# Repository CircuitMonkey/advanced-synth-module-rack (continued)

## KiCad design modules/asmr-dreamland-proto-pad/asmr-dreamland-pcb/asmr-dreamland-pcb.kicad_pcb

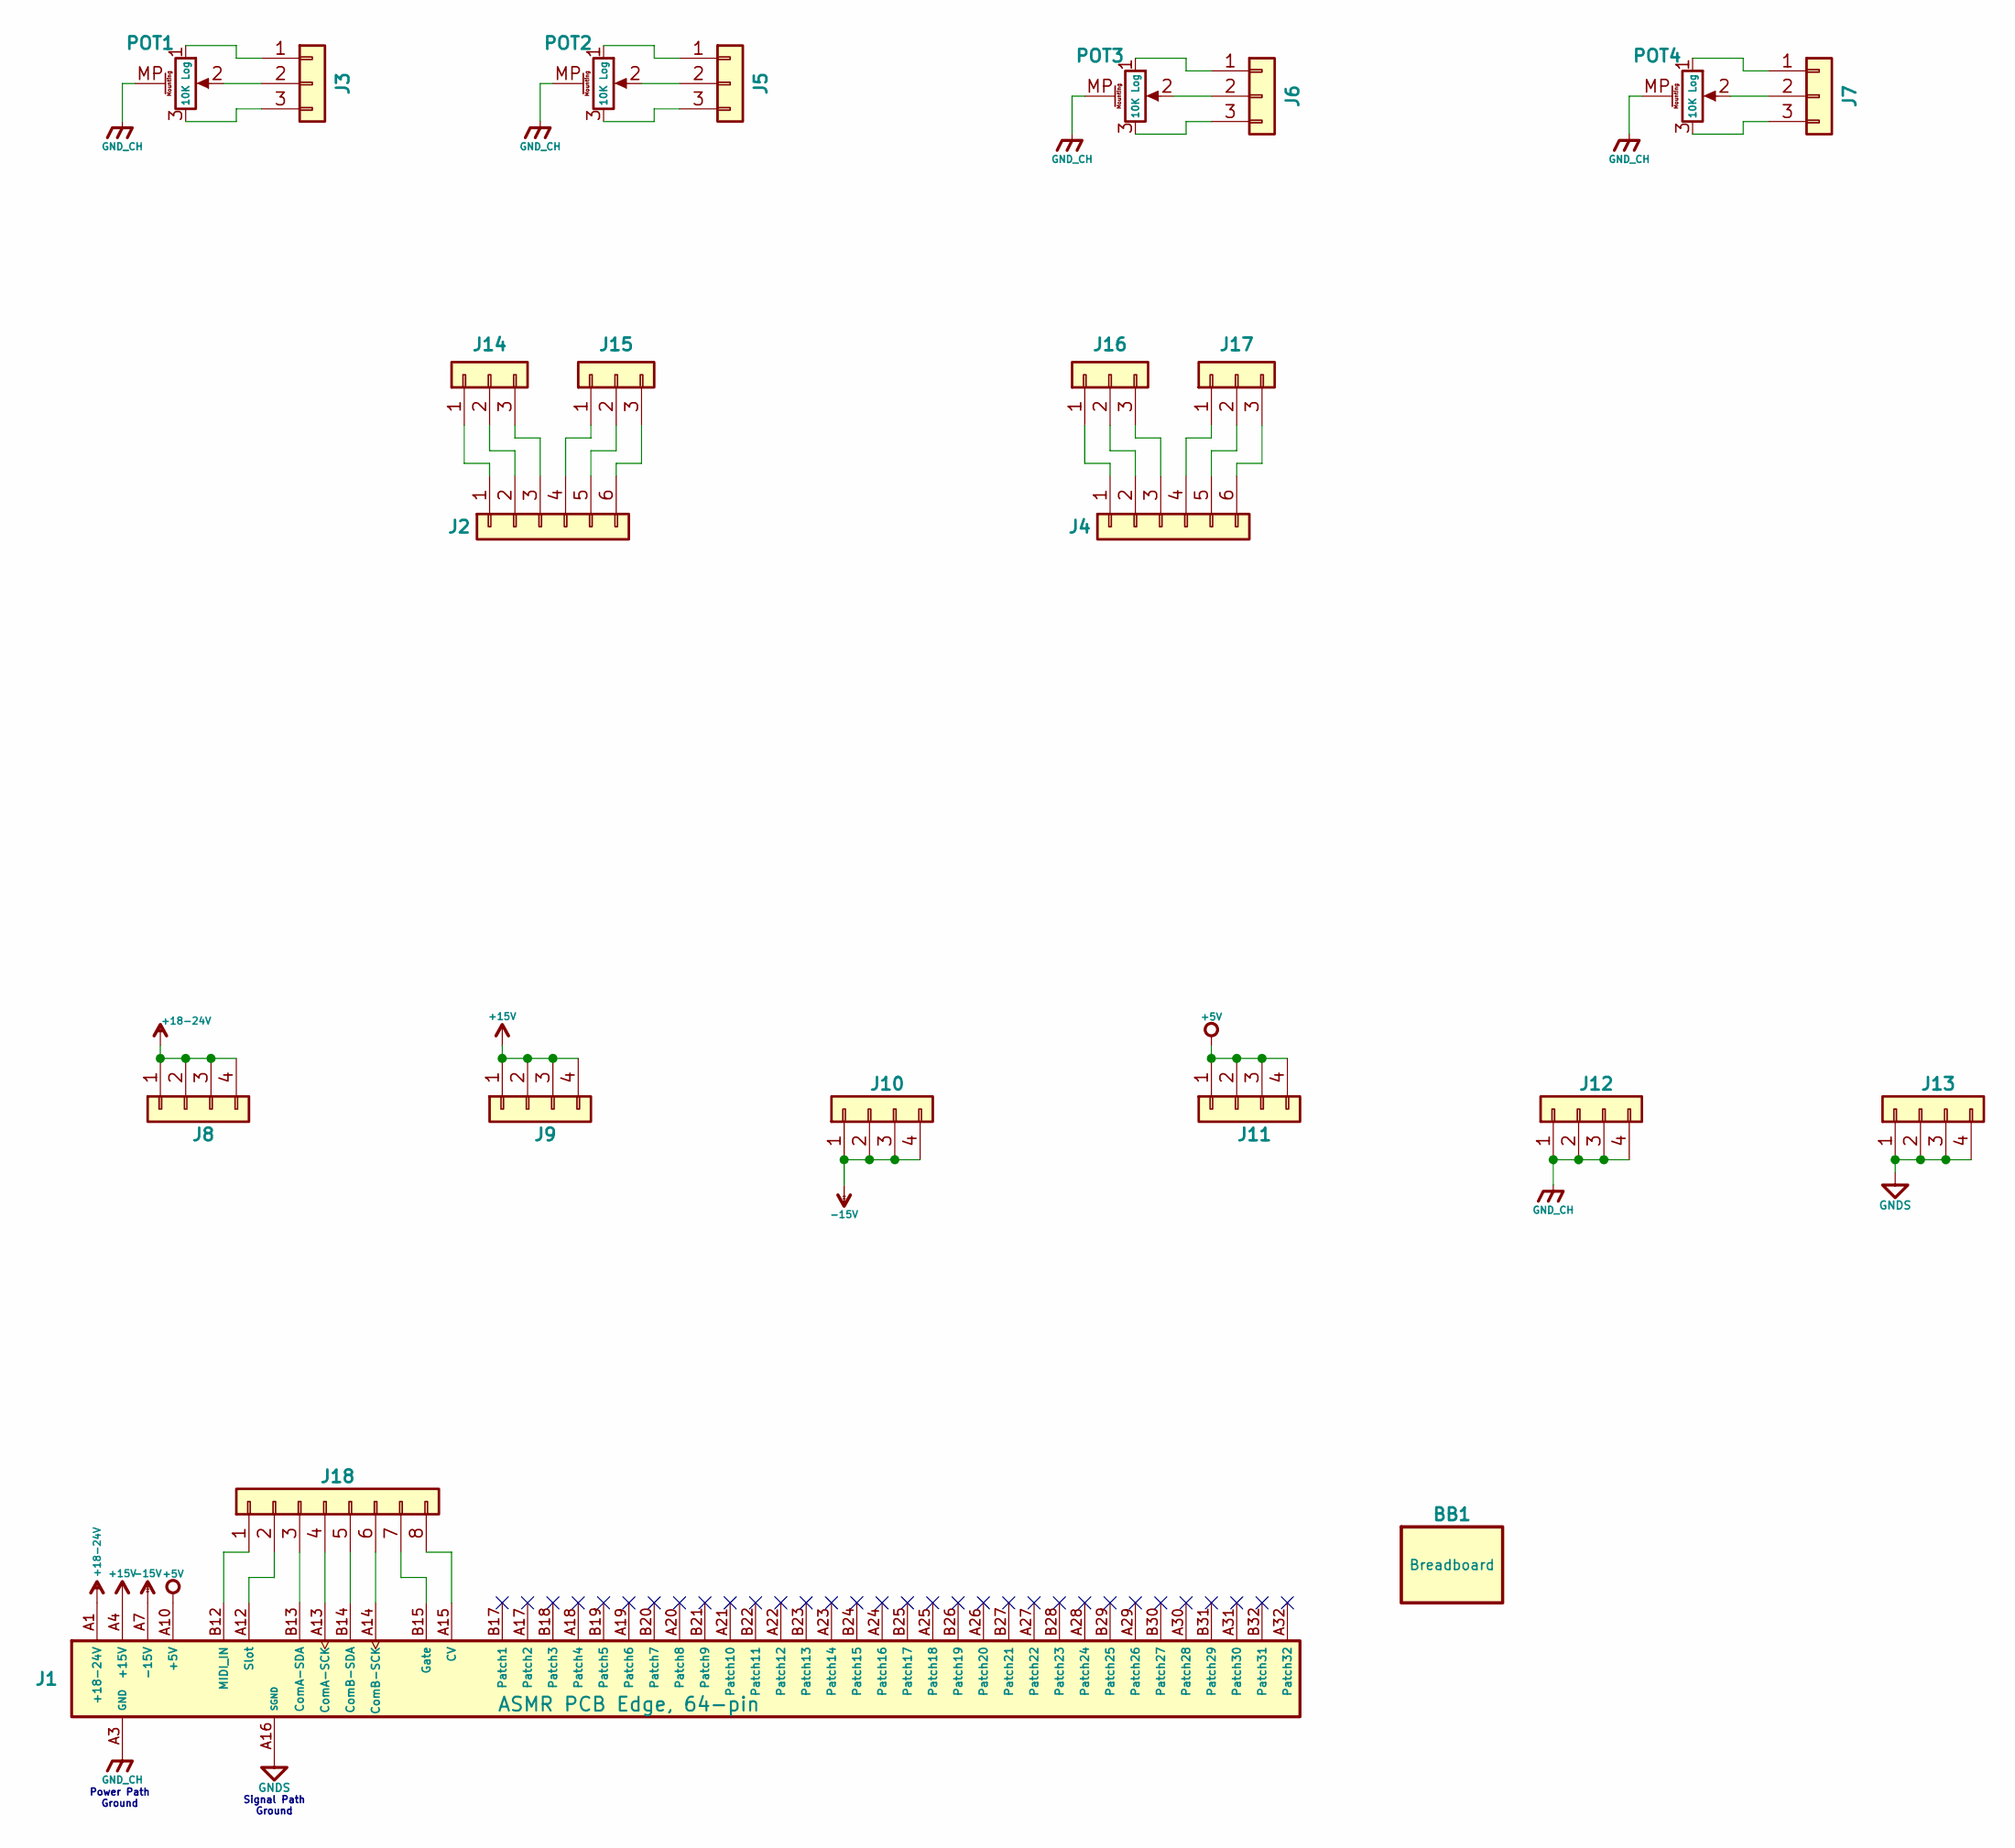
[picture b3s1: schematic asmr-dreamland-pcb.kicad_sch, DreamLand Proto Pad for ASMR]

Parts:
BB1: Breadboard; breadboard-84x55; MPN Tayda A-1427 (or similar)
J1: ASMR-Edge-64
J2, J4: Conn_01x06; PinSocket_1x06_P2.54mm_Vertical
J3, J5, J6, J7: Conn_01x03; PinSocket_1x03_P2.54mm_Vertical
J8, J9, J10, J11, J12, J13: Conn_01x10; PinSocket_1x04_P2.54mm_Vertical
J14, J15, J16, J17: Conn_01x03; PinHeader_1x03_P2.54mm_Vertical
J18: Conn_01x08; PinSocket_1x08_P2.54mm_Vertical
POT1, POT2, POT3, POT4: 10K Log; pot-thd-ra-11mm

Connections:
+5V: J1.A10 (+5V), J1.A11 (+5V), J1.B10 (+5V), J1.B11 (+5V), J11.1, J11.2, J11.3, J11.4
+15V: J1.A4 (+15V), J1.A5 (+15V), J1.B4 (+15V), J1.B5 (+15V), J9.1, J9.2, J9.3, J9.4
+18-24V: J1.A1 (+18-24V), J1.A2 (+18-24V), J1.B1 (+18-24V), J1.B2 (+18-24V), J8.1, J8.2, J8.3, J8.4
-15V: J1.A7 (-15V), J1.A8 (-15V), J1.B7 (-15V), J1.B8 (-15V), J10.1, J10.2, J10.3, J10.4
GNDS: J1.A16 (SGND), J1.B16 (SGND), J13.1, J13.2, J13.3, J13.4
GND_CH: J1.A3 (GND), J1.A6 (GND), J1.A9 (GND), J1.B3 (GND), J1.B6 (GND), J1.B9 (GND), J12.1, J12.2, J12.3, J12.4, POT1.MP (MountPin), POT2.MP (MountPin), POT3.MP (MountPin), POT4.MP (MountPin)
unnamed: J1.A15 (CV), J18.8
unnamed: J1.A13 (ComA-SCK), J18.4
unnamed: J1.B13 (ComA-SDA), J18.3
unnamed: J1.A14 (ComB-SCK), J18.6
unnamed: J1.B14 (ComB-SDA), J18.5
unnamed: J1.B15 (Gate), J18.7
unnamed: J1.B12 (MIDI_IN), J18.1
unnamed: J1.A12 (Slot), J18.2
unnamed: J3.1, POT1.1
unnamed: J3.2, POT1.2
unnamed: J3.3, POT1.3
unnamed: J5.1, POT2.1
unnamed: J5.2, POT2.2
unnamed: J5.3, POT2.3
unnamed: J6.1, POT3.1
unnamed: J6.2, POT3.2
unnamed: J6.3, POT3.3
unnamed: J7.1, POT4.1
unnamed: J7.2, POT4.2
unnamed: J7.3, POT4.3
unnamed: J2.1, J14.1
unnamed: J2.2, J14.2
unnamed: J2.3, J14.3
unnamed: J2.4, J15.1
unnamed: J2.5, J15.2
unnamed: J2.6, J15.3
unnamed: J4.1, J16.1
unnamed: J4.2, J16.2
unnamed: J4.3, J16.3
unnamed: J4.4, J17.1
unnamed: J4.5, J17.2
unnamed: J4.6, J17.3

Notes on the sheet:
Power Path Ground
Signal Path Ground

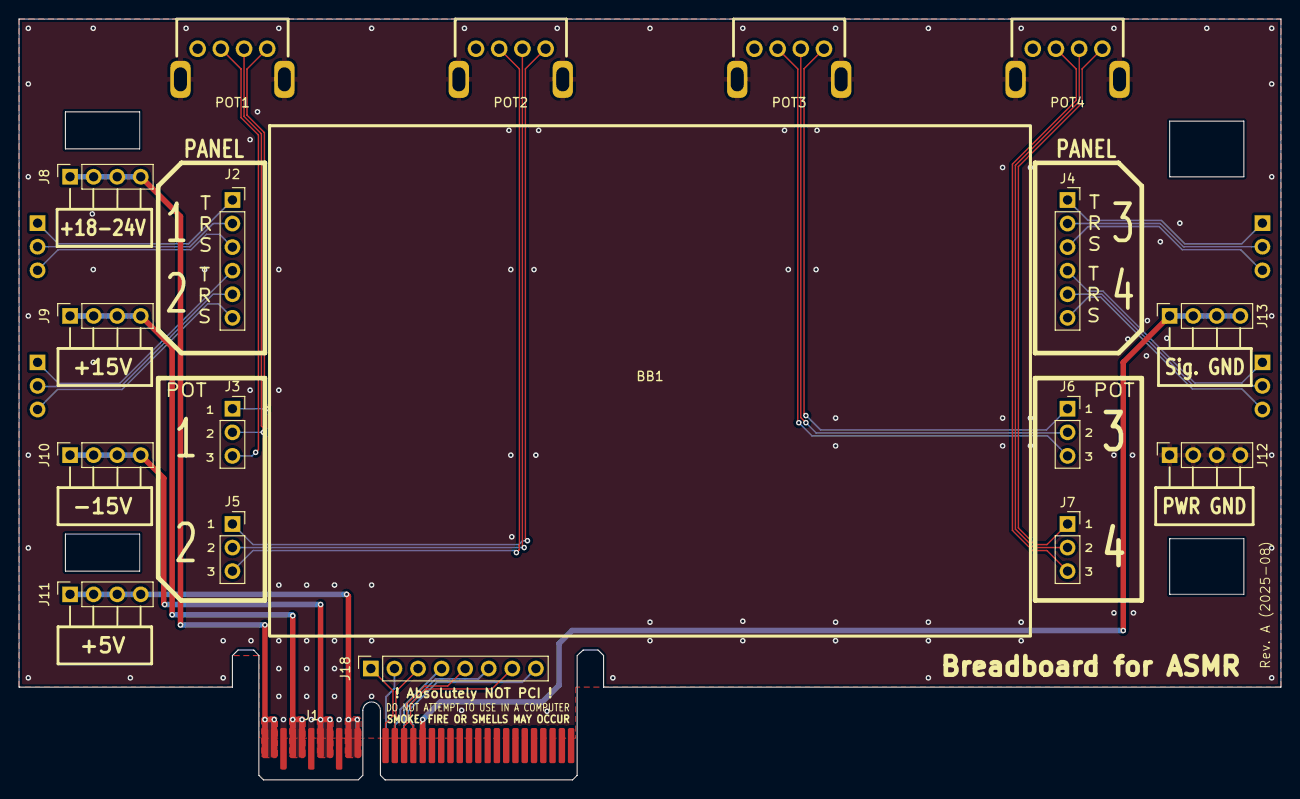
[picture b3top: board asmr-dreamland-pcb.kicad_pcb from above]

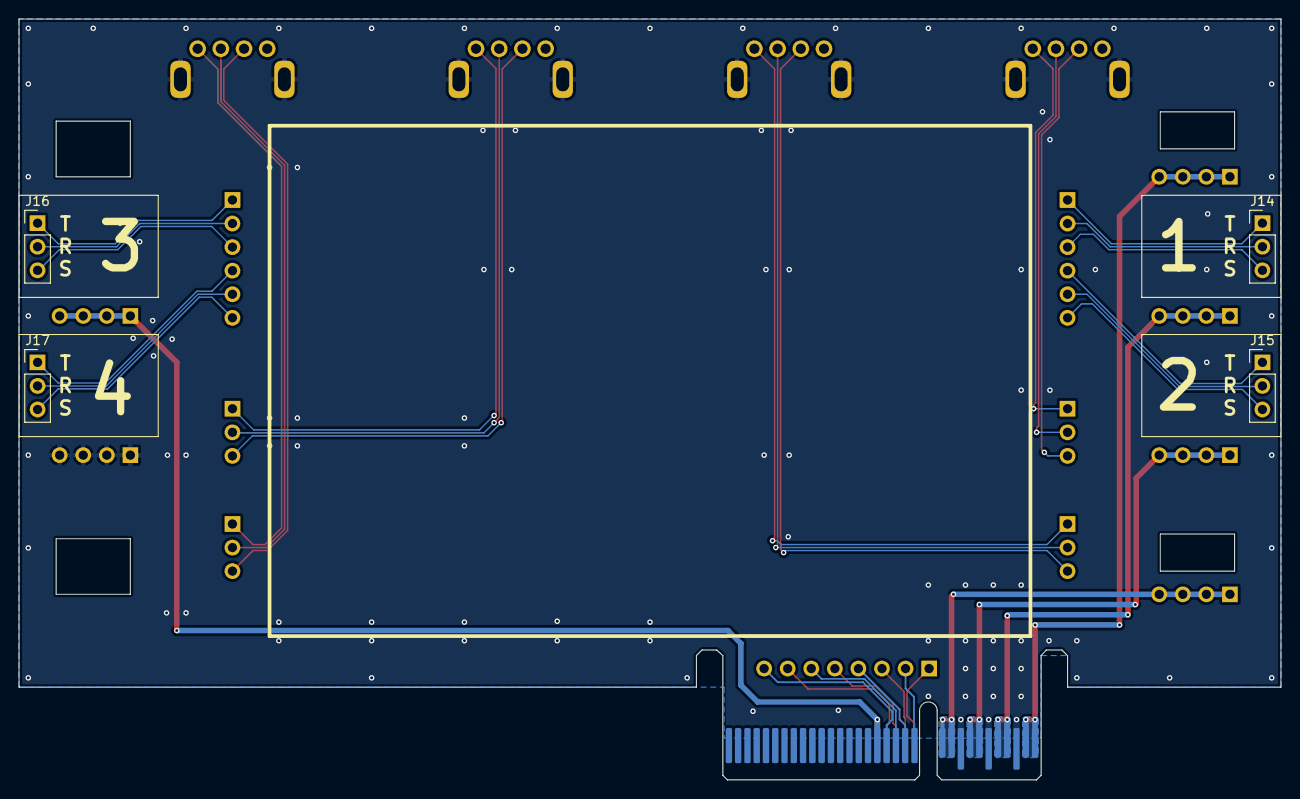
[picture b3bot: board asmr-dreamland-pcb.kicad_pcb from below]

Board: 2 copper layers, 136.0 x 82.0 mm, 23 parts (4 on the bottom side), 38 nets.

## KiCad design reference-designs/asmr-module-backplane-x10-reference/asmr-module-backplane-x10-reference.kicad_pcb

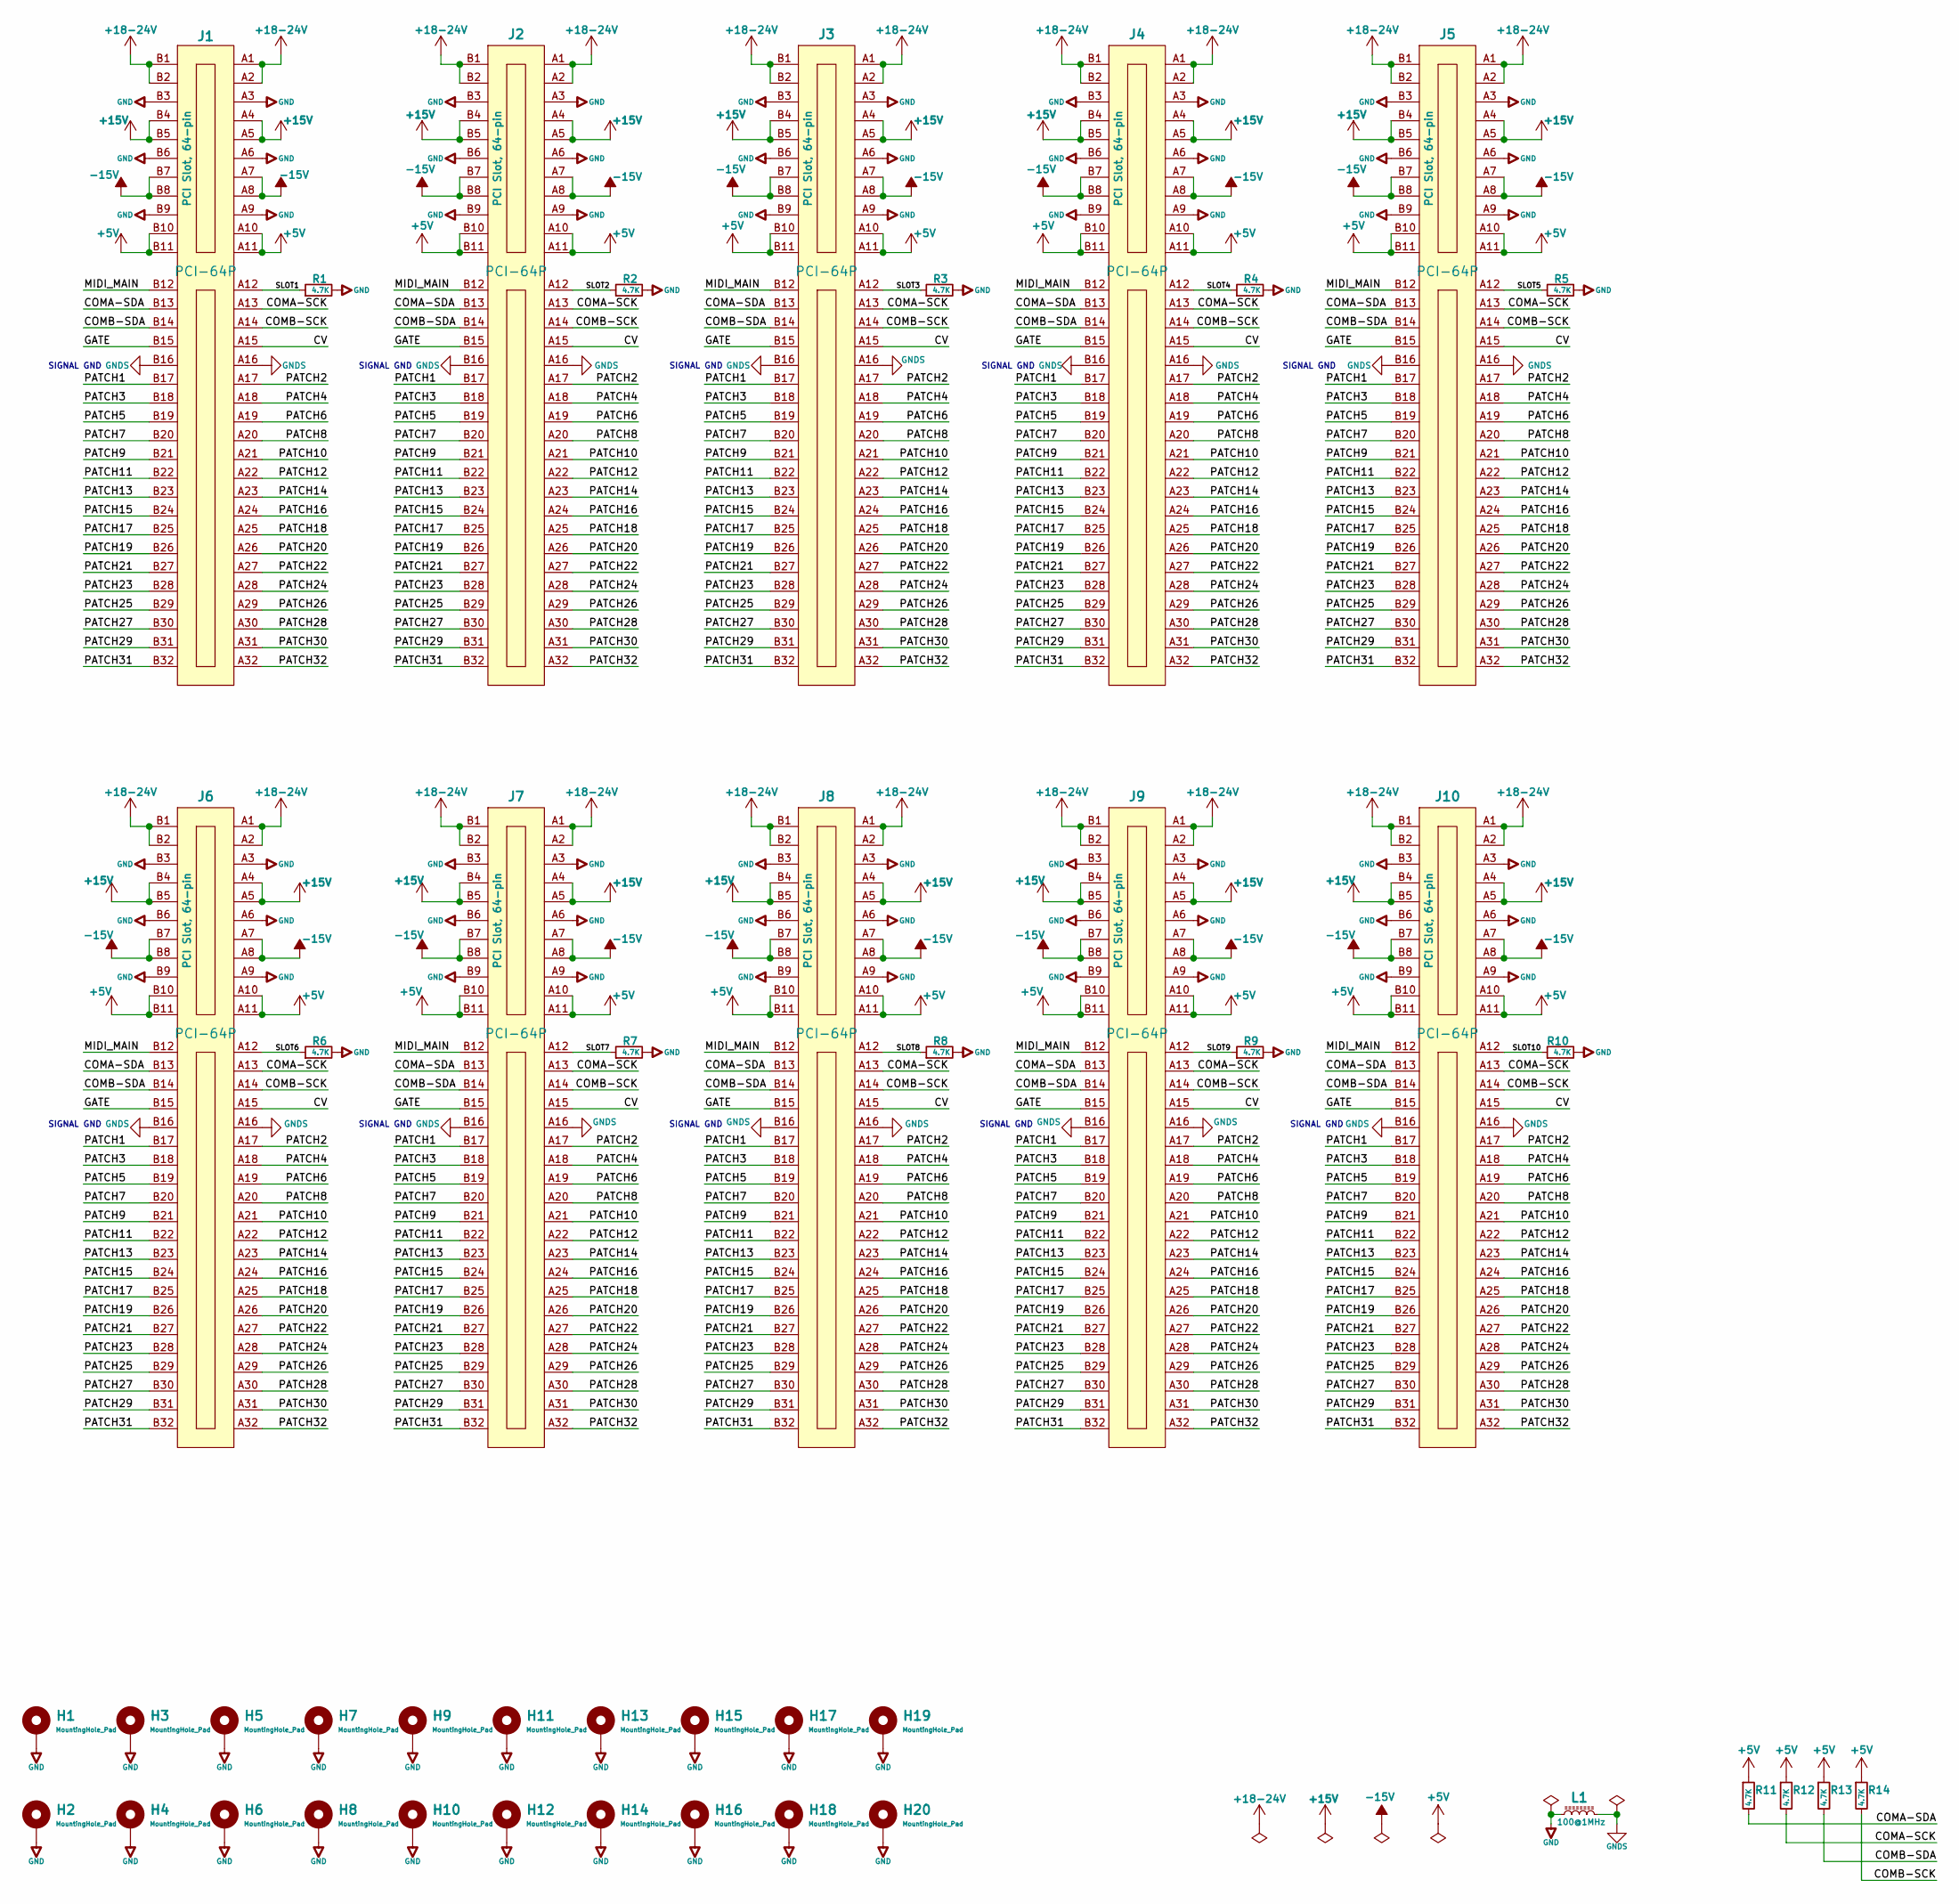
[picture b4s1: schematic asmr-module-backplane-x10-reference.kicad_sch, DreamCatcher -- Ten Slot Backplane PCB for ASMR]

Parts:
H1, H2, H3, H4, H5, H6, H7, H8, H9, H10, H11, H12, H13, H14, H15, H16, H17, H18, H19, H20: MountingHole_Pad; MountingHole_3.2mm_M3_Pad_TopBottom
J1, J2, J3, J4, J5, J6, J7, J8, J9, J10: PCI-64P; PCI-Slot-64-THD-FCI-10018784; MPN 10018783-10201TLF
L1: 100@1MHz; R_0603_1608Metric
R1, R2, R3, R4, R5, R6, R7, R8, R9, R10, R11, R12, R13, R14: 4.7K; R_0603_1608Metric

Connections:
+5V: J1.A10, J1.A11, J1.B10, J1.B11, J2.A10, J2.A11, J2.B10, J2.B11, J3.A10, J3.A11, J3.B10, J3.B11, J4.A10, J4.A11, J4.B10, J4.B11, J5.A10, J5.A11, J5.B10, J5.B11, J6.A10, J6.A11, J6.B10, J6.B11, J7.A10, J7.A11, J7.B10, J7.B11, J8.A10, J8.A11, J8.B10, J8.B11, J9.A10, J9.A11, J9.B10, J9.B11, J10.A10, J10.A11, J10.B10, J10.B11, R11.1, R12.1, R13.1, R14.1
+15V: J1.A4, J1.A5, J1.B4, J1.B5, J2.A4, J2.A5, J2.B4, J2.B5, J3.A4, J3.A5, J3.B4, J3.B5, J4.A4, J4.A5, J4.B4, J4.B5, J5.A4, J5.A5, J5.B4, J5.B5, J6.A4, J6.A5, J6.B4, J6.B5, J7.A4, J7.A5, J7.B4, J7.B5, J8.A4, J8.A5, J8.B4, J8.B5, J9.A4, J9.A5, J9.B4, J9.B5, J10.A4, J10.A5, J10.B4, J10.B5
+18-24V: J1.A1, J1.A2, J1.B1, J1.B2, J2.A1, J2.A2, J2.B1, J2.B2, J3.A1, J3.A2, J3.B1, J3.B2, J4.A1, J4.A2, J4.B1, J4.B2, J5.A1, J5.A2, J5.B1, J5.B2, J6.A1, J6.A2, J6.B1, J6.B2, J7.A1, J7.A2, J7.B1, J7.B2, J8.A1, J8.A2, J8.B1, J8.B2, J9.A1, J9.A2, J9.B1, J9.B2, J10.A1, J10.A2, J10.B1, J10.B2
-15V: J1.A7, J1.A8, J1.B7, J1.B8, J2.A7, J2.A8, J2.B7, J2.B8, J3.A7, J3.A8, J3.B7, J3.B8, J4.A7, J4.A8, J4.B7, J4.B8, J5.A7, J5.A8, J5.B7, J5.B8, J6.A7, J6.A8, J6.B7, J6.B8, J7.A7, J7.A8, J7.B7, J7.B8, J8.A7, J8.A8, J8.B7, J8.B8, J9.A7, J9.A8, J9.B7, J9.B8, J10.A7, J10.A8, J10.B7, J10.B8
/COMA-SCK: J1.A13, J2.A13, J3.A13, J4.A13, J5.A13, J6.A13, J7.A13, J8.A13, J9.A13, J10.A13, R12.2
/COMA-SDA: J1.B13, J2.B13, J3.B13, J4.B13, J5.B13, J6.B13, J7.B13, J8.B13, J9.B13, J10.B13, R11.2
/COMB-SCK: J1.A14, J2.A14, J3.A14, J4.A14, J5.A14, J6.A14, J7.A14, J8.A14, J9.A14, J10.A14, R14.2
/COMB-SDA: J1.B14, J2.B14, J3.B14, J4.B14, J5.B14, J6.B14, J7.B14, J8.B14, J9.B14, J10.B14, R13.2
/CV: J1.A15, J2.A15, J3.A15, J4.A15, J5.A15, J6.A15, J7.A15, J8.A15, J9.A15, J10.A15
/GATE: J1.B15, J2.B15, J3.B15, J4.B15, J5.B15, J6.B15, J7.B15, J8.B15, J9.B15, J10.B15
/MIDI_MAIN: J1.B12, J2.B12, J3.B12, J4.B12, J5.B12, J6.B12, J7.B12, J8.B12, J9.B12, J10.B12
/PATCH1: J1.B17, J2.B17, J3.B17, J4.B17, J5.B17, J6.B17, J7.B17, J8.B17, J9.B17, J10.B17
/PATCH2: J1.A17, J2.A17, J3.A17, J4.A17, J5.A17, J6.A17, J7.A17, J8.A17, J9.A17, J10.A17
/PATCH3: J1.B18, J2.B18, J3.B18, J4.B18, J5.B18, J6.B18, J7.B18, J8.B18, J9.B18, J10.B18
/PATCH4: J1.A18, J2.A18, J3.A18, J4.A18, J5.A18, J6.A18, J7.A18, J8.A18, J9.A18, J10.A18
/PATCH5: J1.B19, J2.B19, J3.B19, J4.B19, J5.B19, J6.B19, J7.B19, J8.B19, J9.B19, J10.B19
/PATCH6: J1.A19, J2.A19, J3.A19, J4.A19, J5.A19, J6.A19, J7.A19, J8.A19, J9.A19, J10.A19
/PATCH7: J1.B20, J2.B20, J3.B20, J4.B20, J5.B20, J6.B20, J7.B20, J8.B20, J9.B20, J10.B20
/PATCH8: J1.A20, J2.A20, J3.A20, J4.A20, J5.A20, J6.A20, J7.A20, J8.A20, J9.A20, J10.A20
/PATCH9: J1.B21, J2.B21, J3.B21, J4.B21, J5.B21, J6.B21, J7.B21, J8.B21, J9.B21, J10.B21
/PATCH10: J1.A21, J2.A21, J3.A21, J4.A21, J5.A21, J6.A21, J7.A21, J8.A21, J9.A21, J10.A21
/PATCH11: J1.B22, J2.B22, J3.B22, J4.B22, J5.B22, J6.B22, J7.B22, J8.B22, J9.B22, J10.B22
/PATCH12: J1.A22, J2.A22, J3.A22, J4.A22, J5.A22, J6.A22, J7.A22, J8.A22, J9.A22, J10.A22
/PATCH13: J1.B23, J2.B23, J3.B23, J4.B23, J5.B23, J6.B23, J7.B23, J8.B23, J9.B23, J10.B23
/PATCH14: J1.A23, J2.A23, J3.A23, J4.A23, J5.A23, J6.A23, J7.A23, J8.A23, J9.A23, J10.A23
/PATCH15: J1.B24, J2.B24, J3.B24, J4.B24, J5.B24, J6.B24, J7.B24, J8.B24, J9.B24, J10.B24
/PATCH16: J1.A24, J2.A24, J3.A24, J4.A24, J5.A24, J6.A24, J7.A24, J8.A24, J9.A24, J10.A24
/PATCH17: J1.B25, J2.B25, J3.B25, J4.B25, J5.B25, J6.B25, J7.B25, J8.B25, J9.B25, J10.B25
/PATCH18: J1.A25, J2.A25, J3.A25, J4.A25, J5.A25, J6.A25, J7.A25, J8.A25, J9.A25, J10.A25
/PATCH19: J1.B26, J2.B26, J3.B26, J4.B26, J5.B26, J6.B26, J7.B26, J8.B26, J9.B26, J10.B26
/PATCH20: J1.A26, J2.A26, J3.A26, J4.A26, J5.A26, J6.A26, J7.A26, J8.A26, J9.A26, J10.A26
/PATCH21: J1.B27, J2.B27, J3.B27, J4.B27, J5.B27, J6.B27, J7.B27, J8.B27, J9.B27, J10.B27
/PATCH22: J1.A27, J2.A27, J3.A27, J4.A27, J5.A27, J6.A27, J7.A27, J8.A27, J9.A27, J10.A27
/PATCH23: J1.B28, J2.B28, J3.B28, J4.B28, J5.B28, J6.B28, J7.B28, J8.B28, J9.B28, J10.B28
/PATCH24: J1.A28, J2.A28, J3.A28, J4.A28, J5.A28, J6.A28, J7.A28, J8.A28, J9.A28, J10.A28
/PATCH25: J1.B29, J2.B29, J3.B29, J4.B29, J5.B29, J6.B29, J7.B29, J8.B29, J9.B29, J10.B29
/PATCH26: J1.A29, J2.A29, J3.A29, J4.A29, J5.A29, J6.A29, J7.A29, J8.A29, J9.A29, J10.A29
/PATCH27: J1.B30, J2.B30, J3.B30, J4.B30, J5.B30, J6.B30, J7.B30, J8.B30, J9.B30, J10.B30
/PATCH28: J1.A30, J2.A30, J3.A30, J4.A30, J5.A30, J6.A30, J7.A30, J8.A30, J9.A30, J10.A30
/PATCH29: J1.B31, J2.B31, J3.B31, J4.B31, J5.B31, J6.B31, J7.B31, J8.B31, J9.B31, J10.B31
/PATCH30: J1.A31, J2.A31, J3.A31, J4.A31, J5.A31, J6.A31, J7.A31, J8.A31, J9.A31, J10.A31
/PATCH31: J1.B32, J2.B32, J3.B32, J4.B32, J5.B32, J6.B32, J7.B32, J8.B32, J9.B32, J10.B32
/PATCH32: J1.A32, J2.A32, J3.A32, J4.A32, J5.A32, J6.A32, J7.A32, J8.A32, J9.A32, J10.A32
/SLOT1: J1.A12, R1.1
/SLOT2: J2.A12, R2.1
/SLOT3: J3.A12, R3.1
/SLOT4: J4.A12, R4.1
/SLOT5: J5.A12, R5.1
/SLOT6: J6.A12, R6.1
/SLOT7: J7.A12, R7.1
/SLOT8: J8.A12, R8.1
/SLOT9: J9.A12, R9.1
/SLOT10: J10.A12, R10.1
GND: H1.1, H2.1, H3.1, H4.1, H5.1, H6.1, H7.1, H8.1, H9.1, H10.1, H11.1, H12.1, H13.1, H14.1, H15.1, H16.1, H17.1, H18.1, H19.1, H20.1, J1.A3, J1.A6, J1.A9, J1.B3, J1.B6, J1.B9, J2.A3, J2.A6, J2.A9, J2.B3, J2.B6, J2.B9, J3.A3, J3.A6, J3.A9, J3.B3, J3.B6, J3.B9, J4.A3, J4.A6, J4.A9, J4.B3, J4.B6, J4.B9, J5.A3, J5.A6, J5.A9, J5.B3, J5.B6, J5.B9, J6.A3, J6.A6, J6.A9, J6.B3, J6.B6, J6.B9, J7.A3, J7.A6, J7.A9, J7.B3, J7.B6, J7.B9, J8.A3, J8.A6, J8.A9, J8.B3, J8.B6, J8.B9, J9.A3, J9.A6, J9.A9, J9.B3, J9.B6, J9.B9, J10.A3, J10.A6, J10.A9, J10.B3, J10.B6, J10.B9, L1.1, R1.2, R2.2, R3.2, R4.2, R5.2, R6.2, R7.2, R8.2, R9.2, R10.2
GNDS: J1.A16, J1.B16, J2.A16, J2.B16, J3.A16, J3.B16, J4.A16, J4.B16, J5.A16, J5.B16, J6.A16, J6.B16, J7.A16, J7.B16, J8.A16, J8.B16, J9.A16, J9.B16, J10.A16, J10.B16, L1.2

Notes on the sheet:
SIGNAL GND

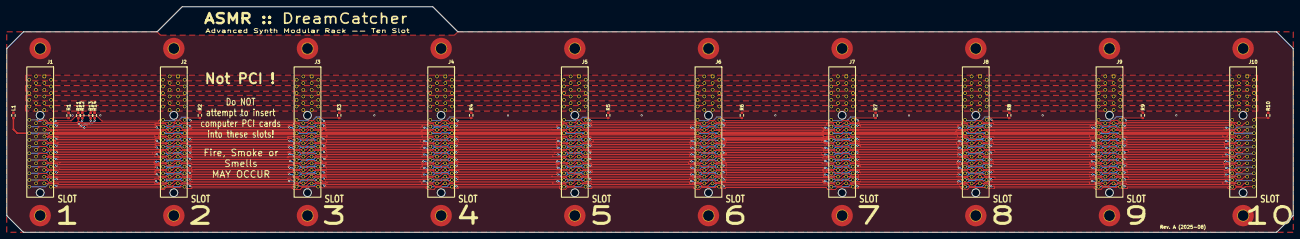
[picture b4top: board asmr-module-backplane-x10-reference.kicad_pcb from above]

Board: 2 copper layers, 385.0 x 67.5 mm, 45 parts (0 on the bottom side), 55 nets.

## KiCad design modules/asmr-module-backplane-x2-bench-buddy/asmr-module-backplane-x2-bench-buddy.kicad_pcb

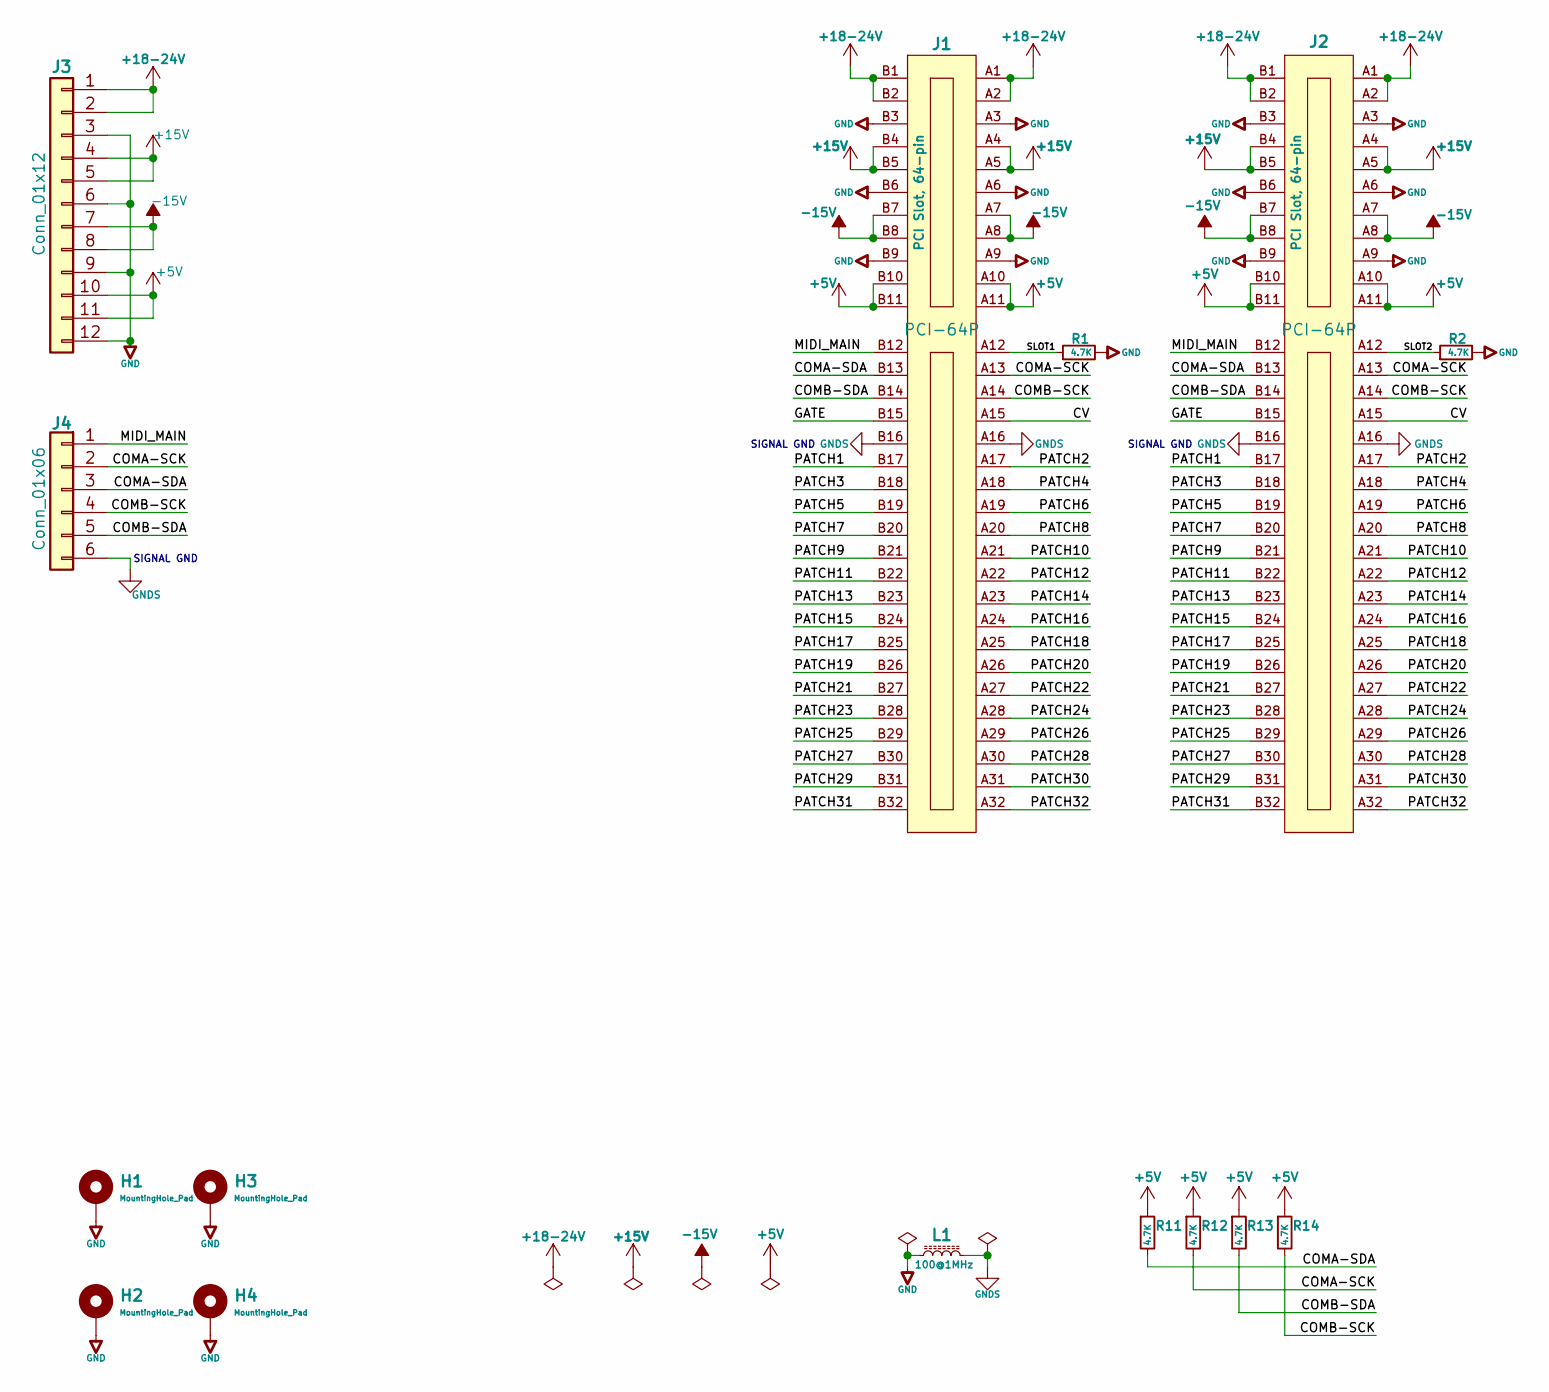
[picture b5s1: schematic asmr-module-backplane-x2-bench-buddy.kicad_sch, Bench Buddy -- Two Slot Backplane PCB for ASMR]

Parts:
H1, H2, H3, H4: MountingHole_Pad; MountingHole_3.2mm_M3_Pad_TopBottom
J1, J2: PCI-64P; PCI-Slot-64-THD-FCI-10018784; MPN 10018783-10201TLF
J3: Conn_01x12; PinHeader_1x12_P2.54mm_Vertical
J4: Conn_01x06; PinHeader_1x06_P2.54mm_Vertical
L1: 100@1MHz; R_0603_1608Metric
R1, R2, R11, R12, R13, R14: 4.7K; R_0603_1608Metric

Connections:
+5V: J1.A10, J1.A11, J1.B10, J1.B11, J2.A10, J2.A11, J2.B10, J2.B11, J3.10, J3.11, R11.1, R12.1, R13.1, R14.1
+15V: J1.A4, J1.A5, J1.B4, J1.B5, J2.A4, J2.A5, J2.B4, J2.B5, J3.4, J3.5
+18-24V: J1.A1, J1.A2, J1.B1, J1.B2, J2.A1, J2.A2, J2.B1, J2.B2, J3.1, J3.2
-15V: J1.A7, J1.A8, J1.B7, J1.B8, J2.A7, J2.A8, J2.B7, J2.B8, J3.7, J3.8
/COMA-SCK: J1.A13, J2.A13, J4.2, R12.2
/COMA-SDA: J1.B13, J2.B13, J4.3, R11.2
/COMB-SCK: J1.A14, J2.A14, J4.4, R14.2
/COMB-SDA: J1.B14, J2.B14, J4.5, R13.2
/CV: J1.A15, J2.A15
/GATE: J1.B15, J2.B15
/MIDI_MAIN: J1.B12, J2.B12, J4.1
/PATCH1: J1.B17, J2.B17
/PATCH2: J1.A17, J2.A17
/PATCH3: J1.B18, J2.B18
/PATCH4: J1.A18, J2.A18
/PATCH5: J1.B19, J2.B19
/PATCH6: J1.A19, J2.A19
/PATCH7: J1.B20, J2.B20
/PATCH8: J1.A20, J2.A20
/PATCH9: J1.B21, J2.B21
/PATCH10: J1.A21, J2.A21
/PATCH11: J1.B22, J2.B22
/PATCH12: J1.A22, J2.A22
/PATCH13: J1.B23, J2.B23
/PATCH14: J1.A23, J2.A23
/PATCH15: J1.B24, J2.B24
/PATCH16: J1.A24, J2.A24
/PATCH17: J1.B25, J2.B25
/PATCH18: J1.A25, J2.A25
/PATCH19: J1.B26, J2.B26
/PATCH20: J1.A26, J2.A26
/PATCH21: J1.B27, J2.B27
/PATCH22: J1.A27, J2.A27
/PATCH23: J1.B28, J2.B28
/PATCH24: J1.A28, J2.A28
/PATCH25: J1.B29, J2.B29
/PATCH26: J1.A29, J2.A29
/PATCH27: J1.B30, J2.B30
/PATCH28: J1.A30, J2.A30
/PATCH29: J1.B31, J2.B31
/PATCH30: J1.A31, J2.A31
/PATCH31: J1.B32, J2.B32
/PATCH32: J1.A32, J2.A32
/SLOT1: J1.A12, R1.1
/SLOT2: J2.A12, R2.1
GND: H1.1, H2.1, H3.1, H4.1, J1.A3, J1.A6, J1.A9, J1.B3, J1.B6, J1.B9, J2.A3, J2.A6, J2.A9, J2.B3, J2.B6, J2.B9, J3.3, J3.6, J3.9, J3.12, L1.1, R1.2, R2.2
GNDS: J1.A16, J1.B16, J2.A16, J2.B16, J4.6, L1.2

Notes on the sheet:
SIGNAL GND

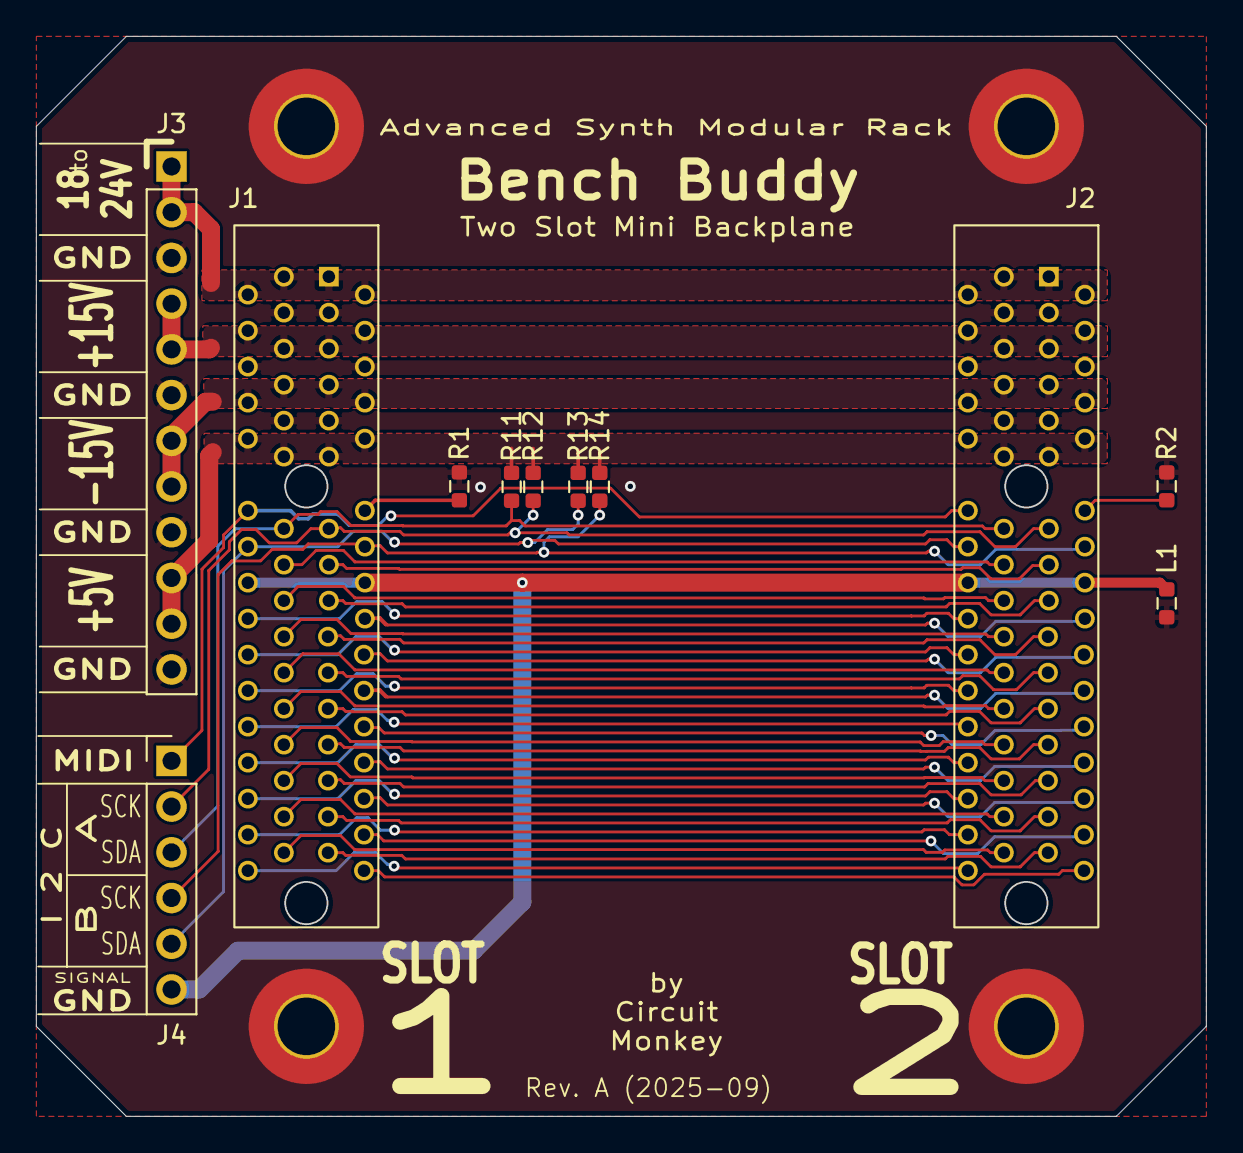
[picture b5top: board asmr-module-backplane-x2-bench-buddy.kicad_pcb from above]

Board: 2 copper layers, 65.0 x 60.0 mm, 15 parts (0 on the bottom side), 47 nets.
